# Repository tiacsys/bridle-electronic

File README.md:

# Bridle's Electronics Corner

<div style="display:flex;justify-content:right;">
<small><em>project update on: <strong>$Format:%cs$ with <mark><a href="https://github.com/tiacsys/bridle-electronic/commits/$Format:%h$" title="$Format:%B$" target="_blank">$Format:%h$</a></mark></strong></em></small>
</div>
<div style="display:flex;justify-content:right;">
<small><em>all data checked on <strong>2022-10-15</strong></em></small>
</div>

## About

This is a storage for all kinds of documentation like manuals, descriptions,
specifications, or datasheets around electronic devices and covers everything
from resistors, semiconductors, boards and assemblies up to finished devices.

## License

<span style="width:128px;float:right;">[![logo]][CC-BY-SA-4.0]</span>

[logo]: electronic/.logos/cc-by-sa.svg "CC-BY-SA"

See [``LICENSE.md``] and [``LICENSE-CC.md``] and also read carefully the
specific ``LICENSE`` or ``COPYRIGHT`` files found in all the subfolders,
if any exist there.

[CC-BY-SA-4.0]: https://creativecommons.org/licenses/by-sa/4.0 "Creative Commons Attribution-ShareAlike 4.0 International"
[``LICENSE-CC.md``]: electronic/LICENSE-CC.md "copy of CC-BY-SA-4.0"
[``LICENSE.md``]: electronic/LICENSE.md "project license"

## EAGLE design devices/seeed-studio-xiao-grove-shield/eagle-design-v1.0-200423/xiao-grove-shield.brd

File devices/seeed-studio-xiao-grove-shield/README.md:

# Grove Shield for Seeed Studio XIAO (Seeeduino XIAO)

<div style="display:flex;justify-content:right;">
<small><em>project update on: <strong>$Format:%cs$ with <mark><a href="https://github.com/tiacsys/bridle-electronic/commits/$Format:%h$" title="$Format:%B$" target="_blank">$Format:%h$</a></mark></strong></em></small>
</div>
<div style="display:flex;justify-content:right;">
<small><em>all data checked on <strong>2022-10-31</strong></em></small>
</div>

## About

<span style="width:256px;float:right;">[![board-iso]][board-iso]</span>

[board-iso]: electronic/devices/seeed-studio-xiao-grove-shield/board-iso.png "Grove Shield for Seeed Studio XIAO"

The **Grove Shield for Seeed Studio XIAO** is a plug-and-play Grove extension
board for [Seeed Studio XIAO][Seeed Studio XIAO SAMD21]. With the on-board power
regulator [ETA3410] and battery management chip [ETA6003] with the battery
bonding pad, you could easily power your Seeed Studio XIAO with lithium battery
and recharge it. 8 Grove connectors onboard includes two Grove I2C and one UART.
It acts as a bridge for Seeed Studio XIAO and [Seeed's Grove System][Grove System].
Flash SPI bonding pad allows you to add Flash to Seeed Studio XIAO to expand its
memory space, providing Seeed Studio XIAO with more possibilities.

[Grove System]: https://wiki.seeedstudio.com/Grove_System "What is the Grove System?"
[ETA3410]: http://www.eta-semi.com/product/1065.html "2A, 3MHz High Efficiency Step-Down Converter"
[ETA6003]: http://www.eta-semi.com/product/908.html "2.5A, 3MHz Switching Charger with Dynamic Power Path Management"

### Compact and Breakable Design

| Compact and Breakable Design |
|::|
| You could even break the board through the onboard PCB stamp holds according to your actual needs of the project (only 25mm x 39mm in dimension after break-off), making it smaller than smaller and the weight would be reduced from 13g to 10g as well! |
| <div style="background-color:white;">[![board-breakable-design]][board-breakable-design]</div> |

[board-breakable-design]: electronic/devices/seeed-studio-xiao-grove-shield/board-breakable-design.png "Grove Shield for Seeed Studio XIAO Breakable Design"

### Supported Boards

| Product | Pin Difference |
|:-|:-|
| [Seeed Studio XIAO SAMD21] | perfectly compatible |
| [Seeed Studio XIAO RP2040] | slightly different |
| [Seeed Studio XIAO ESP32C3] | slightly different |
| [Seeed Studio XIAO nRF52840] | slightly different |
| [Seeed Studio XIAO nRF52840] | slightly different |
| [Seeed Studio XIAO nRF52840 Sense][Seeed Studio XIAO nRF52840] | slightly different |

[Seeed Studio XIAO SAMD21]: index.php?dir=electronic/boards/seeed-studio-xiao-samd21 "Seeed Studio XIAO SAMD21 – Seeeduino XIAO"
[Seeed Studio XIAO RP2040]: index.php?dir=electronic/boards/seeed-studio-xiao-rp2040 "Seeed Studio XIAO RP2040"
[Seeed Studio XIAO ESP32C3]: index.php?dir=electronic/boards/seeed-studio-xiao-esp32c3 "Seeed Studio XIAO ESP32C3"
[Seeed Studio XIAO nRF52840]: index.php?dir=electronic/boards/seeed-studio-xiao-nrf52840 "Seeed Studio XIAO nRF52840"

## References

**EAN**: 6906142379964, 5903351247085<br/>
**UPC**:  906142379964<br/>
**SKU**: 103020312

**HSCODE**:   [8543.70.90.99]<br/>
**EUHSCODE**: [8543.70.90.99]<br/>
**USHSCODE**: [8471.49.00.00]<br/>
**COO**: CHINA

[8543.70.90.99]: https://www.tariffnumber.com/2022/85437090 "HS Code 85437090 – Electrical, machines, apparatus – Other"
[8471.49.00.00]: https://www.tariffnumber.com/2022/84714900 "HS Code 84714900 - Data, processing, machines – Other, presented in the form of systems"

*Brand*: Seeed<br/>
*Part number*: 103020312

* *HTML(2022-10-31)*: [Product Page] – *$4,50 (excl. VAT)*
* *HTML(2022-10-31)*: [Seeed Studio XIAO Series]
  – *Compact and powerful microcontroller*
* *HTML(2022-10-31)*: [Introduction of Grove]
  – *Grove makes it easier to connect, experiment, and simplify the prototyping process*
* *HTML(2022-10-31)*: [Overview of the Seeed Studio XIAO]
  – *Overview of the based Seeed Studio XIAO*

[Product Page]: https://www.seeedstudio.com/Grove-Shield-for-Seeeduino-XIAO-p-4621.html "Grove Shield for Seeed Studio XIAO"
[Seeed Studio XIAO Series]: https://www.seeedstudio.com/xiao-series-page "XIAO: thumb-sized tiny, but powerful"
[Introduction of Grove]: https://www.seeedstudio.com/getting-started.html "Grove: rapid prototyping"
[Overview of the Seeed Studio XIAO]: https://sigmdel.ca/michel/ha/xiao/seeeduino_xiao_01_en.html "Based Seeed Studio XIAO Overview"

| PCB Layer | PCB 3D or Footprint | PCB Populated (top & bottom) |
|::|::|::|
| <div style="background-color:white;"><div style="width:65%;display:inline-block">[![pcb-assembly-pcb]][pcb-assembly-pcb]</div></div> | <div style="background-color:black;"><div style="width:65%;display:inline-block">[![pcb-assembly-3d]][pcb-assembly-3d]</div></div> | <div style="background-color:white;">[![pcb-assembly-top]][pcb-assembly-top]</div> |
|  |  | <div style="background-color:white;">[![pcb-assembly-bot]][pcb-assembly-bot]</div> |

[pcb-assembly-pcb]: electronic/devices/seeed-studio-xiao-grove-shield/pcb-assembly-pcb.png "Grove Shield for Seeed Studio XIAO PCB Layer"
[pcb-assembly-3d]: electronic/devices/seeed-studio-xiao-grove-shield/pcb-assembly-3d.png "Grove Shield for Seeed Studio XIAO PCB 3D"
[pcb-assembly-top]: electronic/devices/seeed-studio-xiao-grove-shield/pcb-assembly-top.png "Grove Shield for Seeed Studio XIAO PCB Assembly (top)"
[pcb-assembly-bot]: electronic/devices/seeed-studio-xiao-grove-shield/pcb-assembly-bot.png "Grove Shield for Seeed Studio XIAO Assembly (bottom)"

## Documentation

* **PDF(2022-10-31)**: [Grove Shield for Seeed Studio XIAO with embedded battery management chip]
  – *[HTML(2022-10-31)](https://wiki.seeedstudio.com/Grove-Shield-for-Seeeduino-XIAO-embedded-battery-management-chip)*

[Grove Shield for Seeed Studio XIAO with embedded battery management chip]: electronic/devices/seeed-studio-xiao-grove-shield/getting-started.pdf "2022-10-31: Last updated on: August 19, 2021"

| Pinout |
|::|
| <div style="background-color:white;"><div style="width:75%;display:inline-block">[![board-pinout]][board-pinout]</div></div> |
| <div style="background-color:white;"><div style="width:75%;display:inline-block">[![board-interfaces]][board-interfaces]</div></div> |
| If you need, use the back of the Seeed Studio XIAO Grove Shield provisions pads for a SPI Flash memory in SOIC8 package. <br/> *Please soldering in right orientation, beginning with **PIN1** as shown below!* |
| <div style="background-color:white;"><div style="width:75%;display:inline-block">[![board-interface-flash]][board-interface-flash]</div></div> |

[board-pinout]: electronic/devices/seeed-studio-xiao-grove-shield/board-pinout.png "Grove Shield for Seeed Studio XIAO Pinout"
[board-interfaces]: electronic/devices/seeed-studio-xiao-grove-shield/board-interfaces.png "Grove Shield for Seeed Studio XIAO Interfaces"
[board-interface-flash]: electronic/devices/seeed-studio-xiao-grove-shield/board-interface-flash.png "Grove Shield for Seeed Studio XIAO Flash memory (SOIC8)"

* **PDF(2022-10-31)**: [Eagle Schematic v1.0 (200423)]
  – *[RAR(2022-10-31)](https://files.seeedstudio.com/wiki/Grove-Shield-for-Seeeduino-XIAO/res/Grove_Shield_for_Seeeduino_XIAO_v1.0.zip)*
  * **ZIP(2022-10-31)**: [Altium Design Data v1.0 (200423)][altium-design-v1.0-200423]
    – *[HTML(2022-10-31)](https://wiki.seeedstudio.com/Grove-Shield-for-Seeeduino-XIAO-embedded-battery-management-chip/#schematic-online-viewer)*

[Eagle Schematic v1.0 (200423)]: electronic/devices/seeed-studio-xiao-grove-shield/eagle-design-v1.0-200423/xiao-grove-shield-schematic.pdf "2022-10-31: Last updated on: April 23, 2020"

| Revision | Design Data | PCB Layout | Changelog |
|::|:-|::|:-|
| **v1.0** – *(September 2021)* | [eagle-design-v1.0-200423]:<br/>- [SCH-1-0]<br/>- [BRD-1-0] | <div style="background-color:black;"><div style="width:100%;display:inline-block">[![eagle-board-v1.0-200423]][eagle-board-v1.0-200423]</div></div> | Initail Version |
| | [altium-design-v1.0-200423]:<br/>- [PrjPcb-ZIP]<br/>- [STEP-1-0] | | |

[eagle-design-v1.0-200423]: index.php?dir=electronic/devices/seeed-studio-xiao-grove-shield/eagle-design-v1.0-200423 "Eagle Design Data"
[SCH-1-0]: electronic/devices/seeed-studio-xiao-grove-shield/eagle-design-v1.0-200423/xiao-grove-shield.sch "Eagle v9.3.1 Schematic"
[BRD-1-0]: electronic/devices/seeed-studio-xiao-grove-shield/eagle-design-v1.0-200423/xiao-grove-shield.brd "Eagle v9.3.1 Board"
[eagle-board-v1.0-200423]: electronic/devices/seeed-studio-xiao-grove-shield/eagle-design-v1.0-200423/xiao-grove-shield-pcb.svg "2022-10-31: Last updated on: April 23, 2020"

[altium-design-v1.0-200423]: index.php?dir=electronic/devices/seeed-studio-xiao-grove-shield/altium-design-v1.0-200423 "Altium Design Data"
[PrjPcb-ZIP]: electronic/devices/seeed-studio-xiao-grove-shield/altium-design-v1.0-200423/xiao-grove-shield-altium-designer.zip "Altium Designer Project Archive"
[STEP-1-0]: electronic/devices/seeed-studio-xiao-grove-shield/altium-design-v1.0-200423/xiao-grove-shield-pcb.step "Open CASCADE STEP processor 6.8"

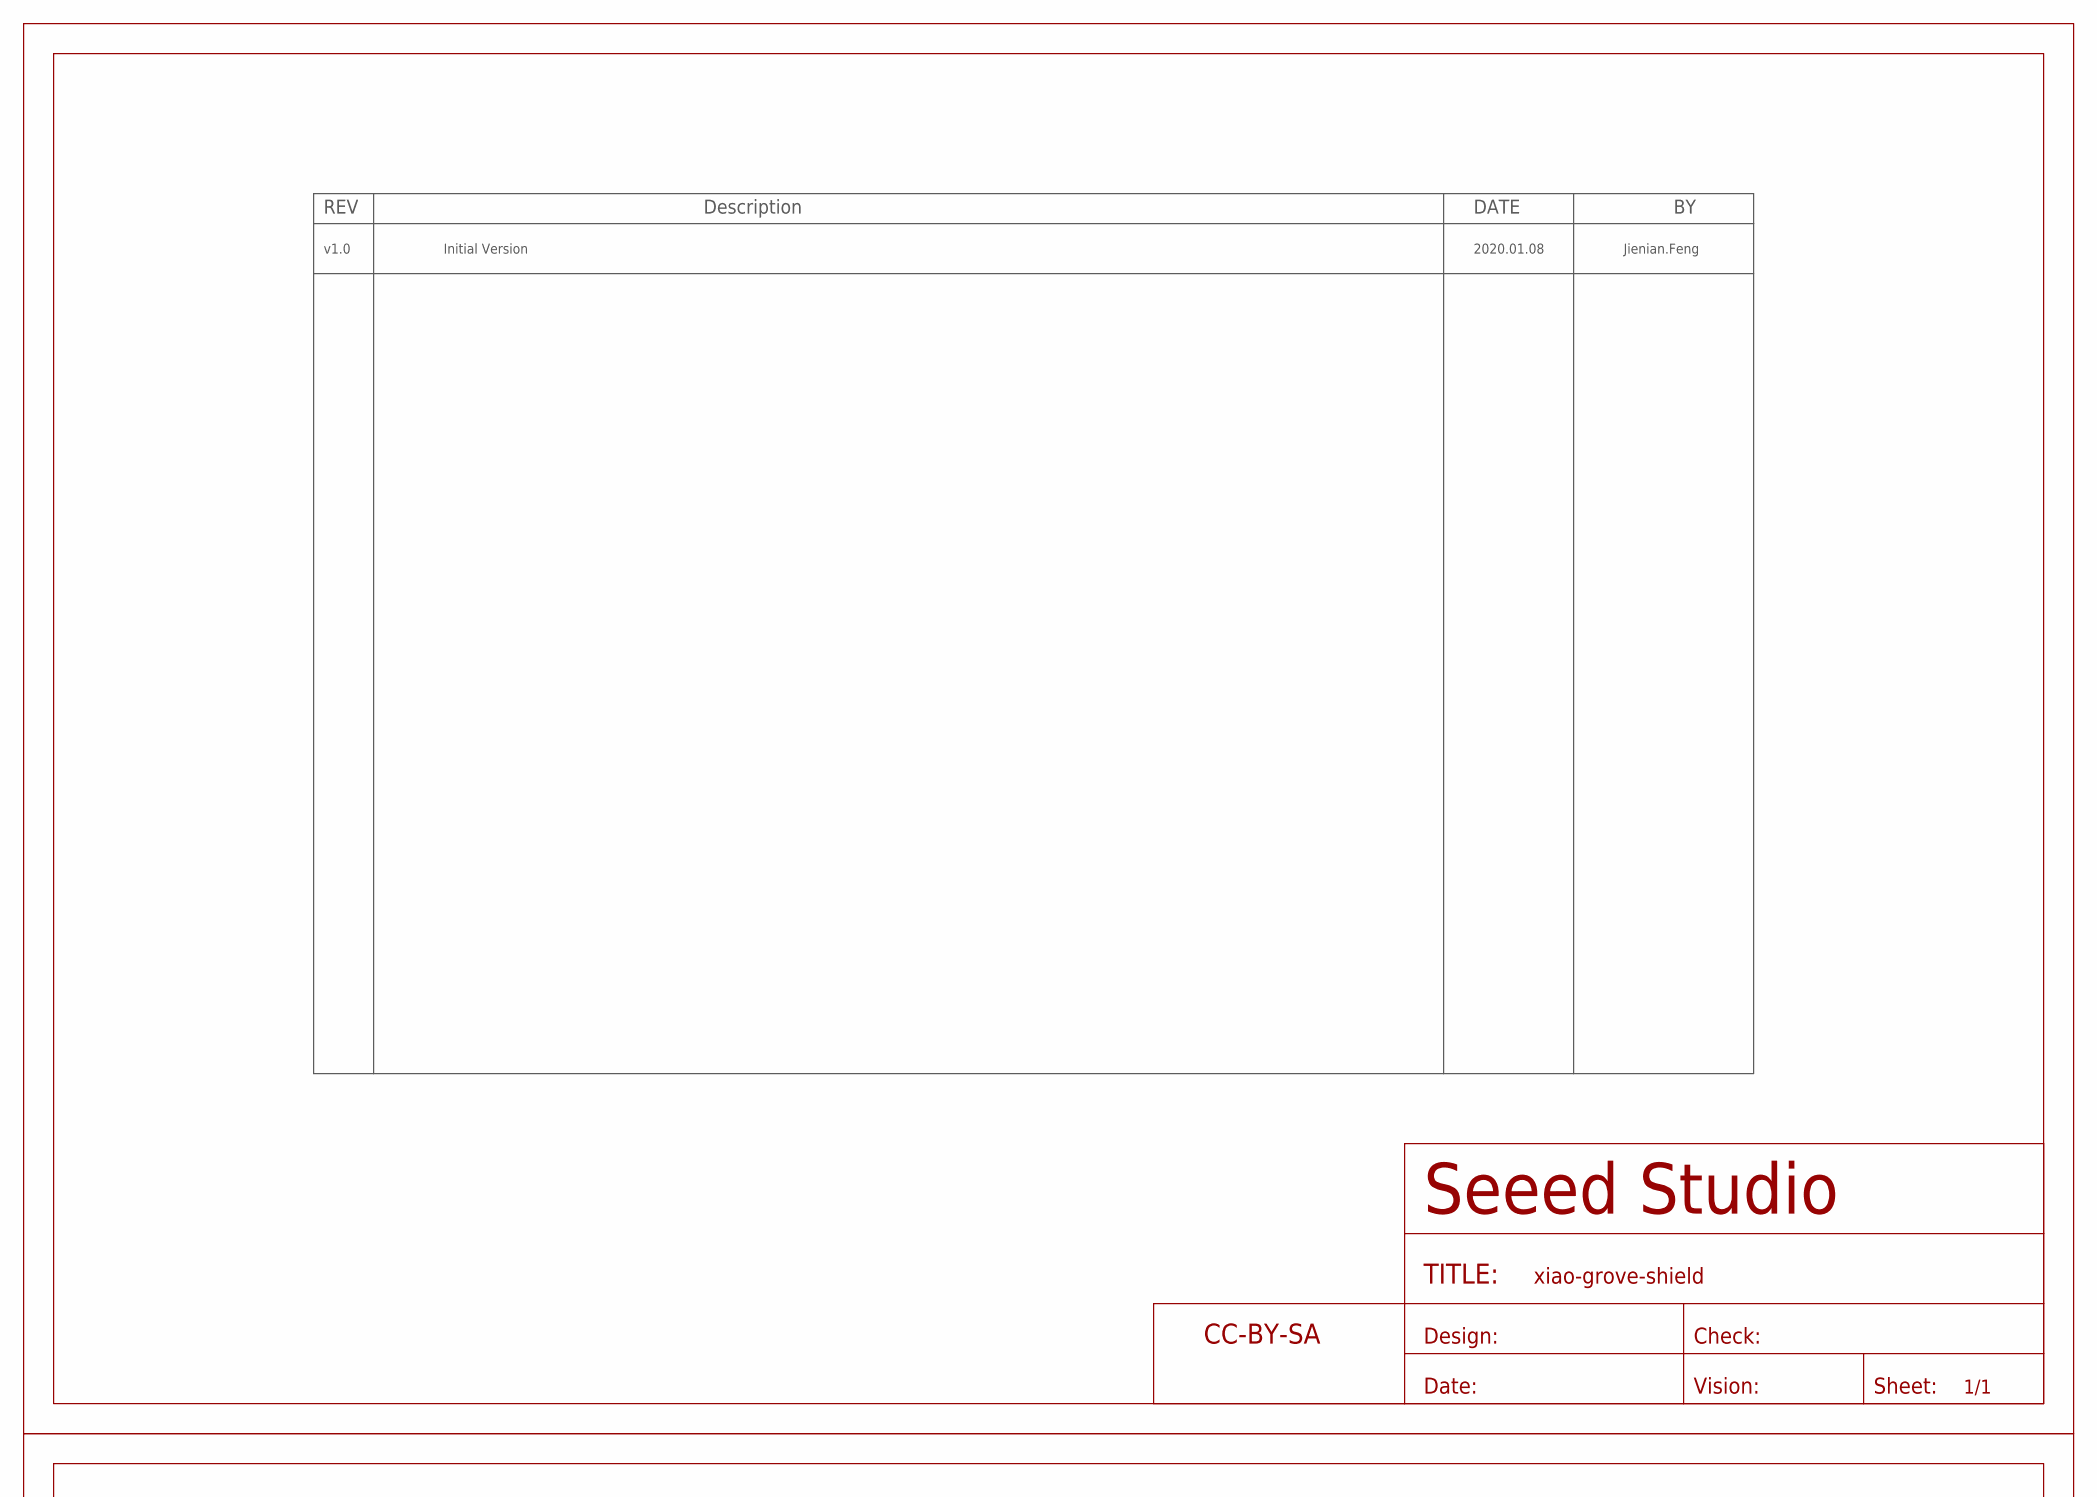
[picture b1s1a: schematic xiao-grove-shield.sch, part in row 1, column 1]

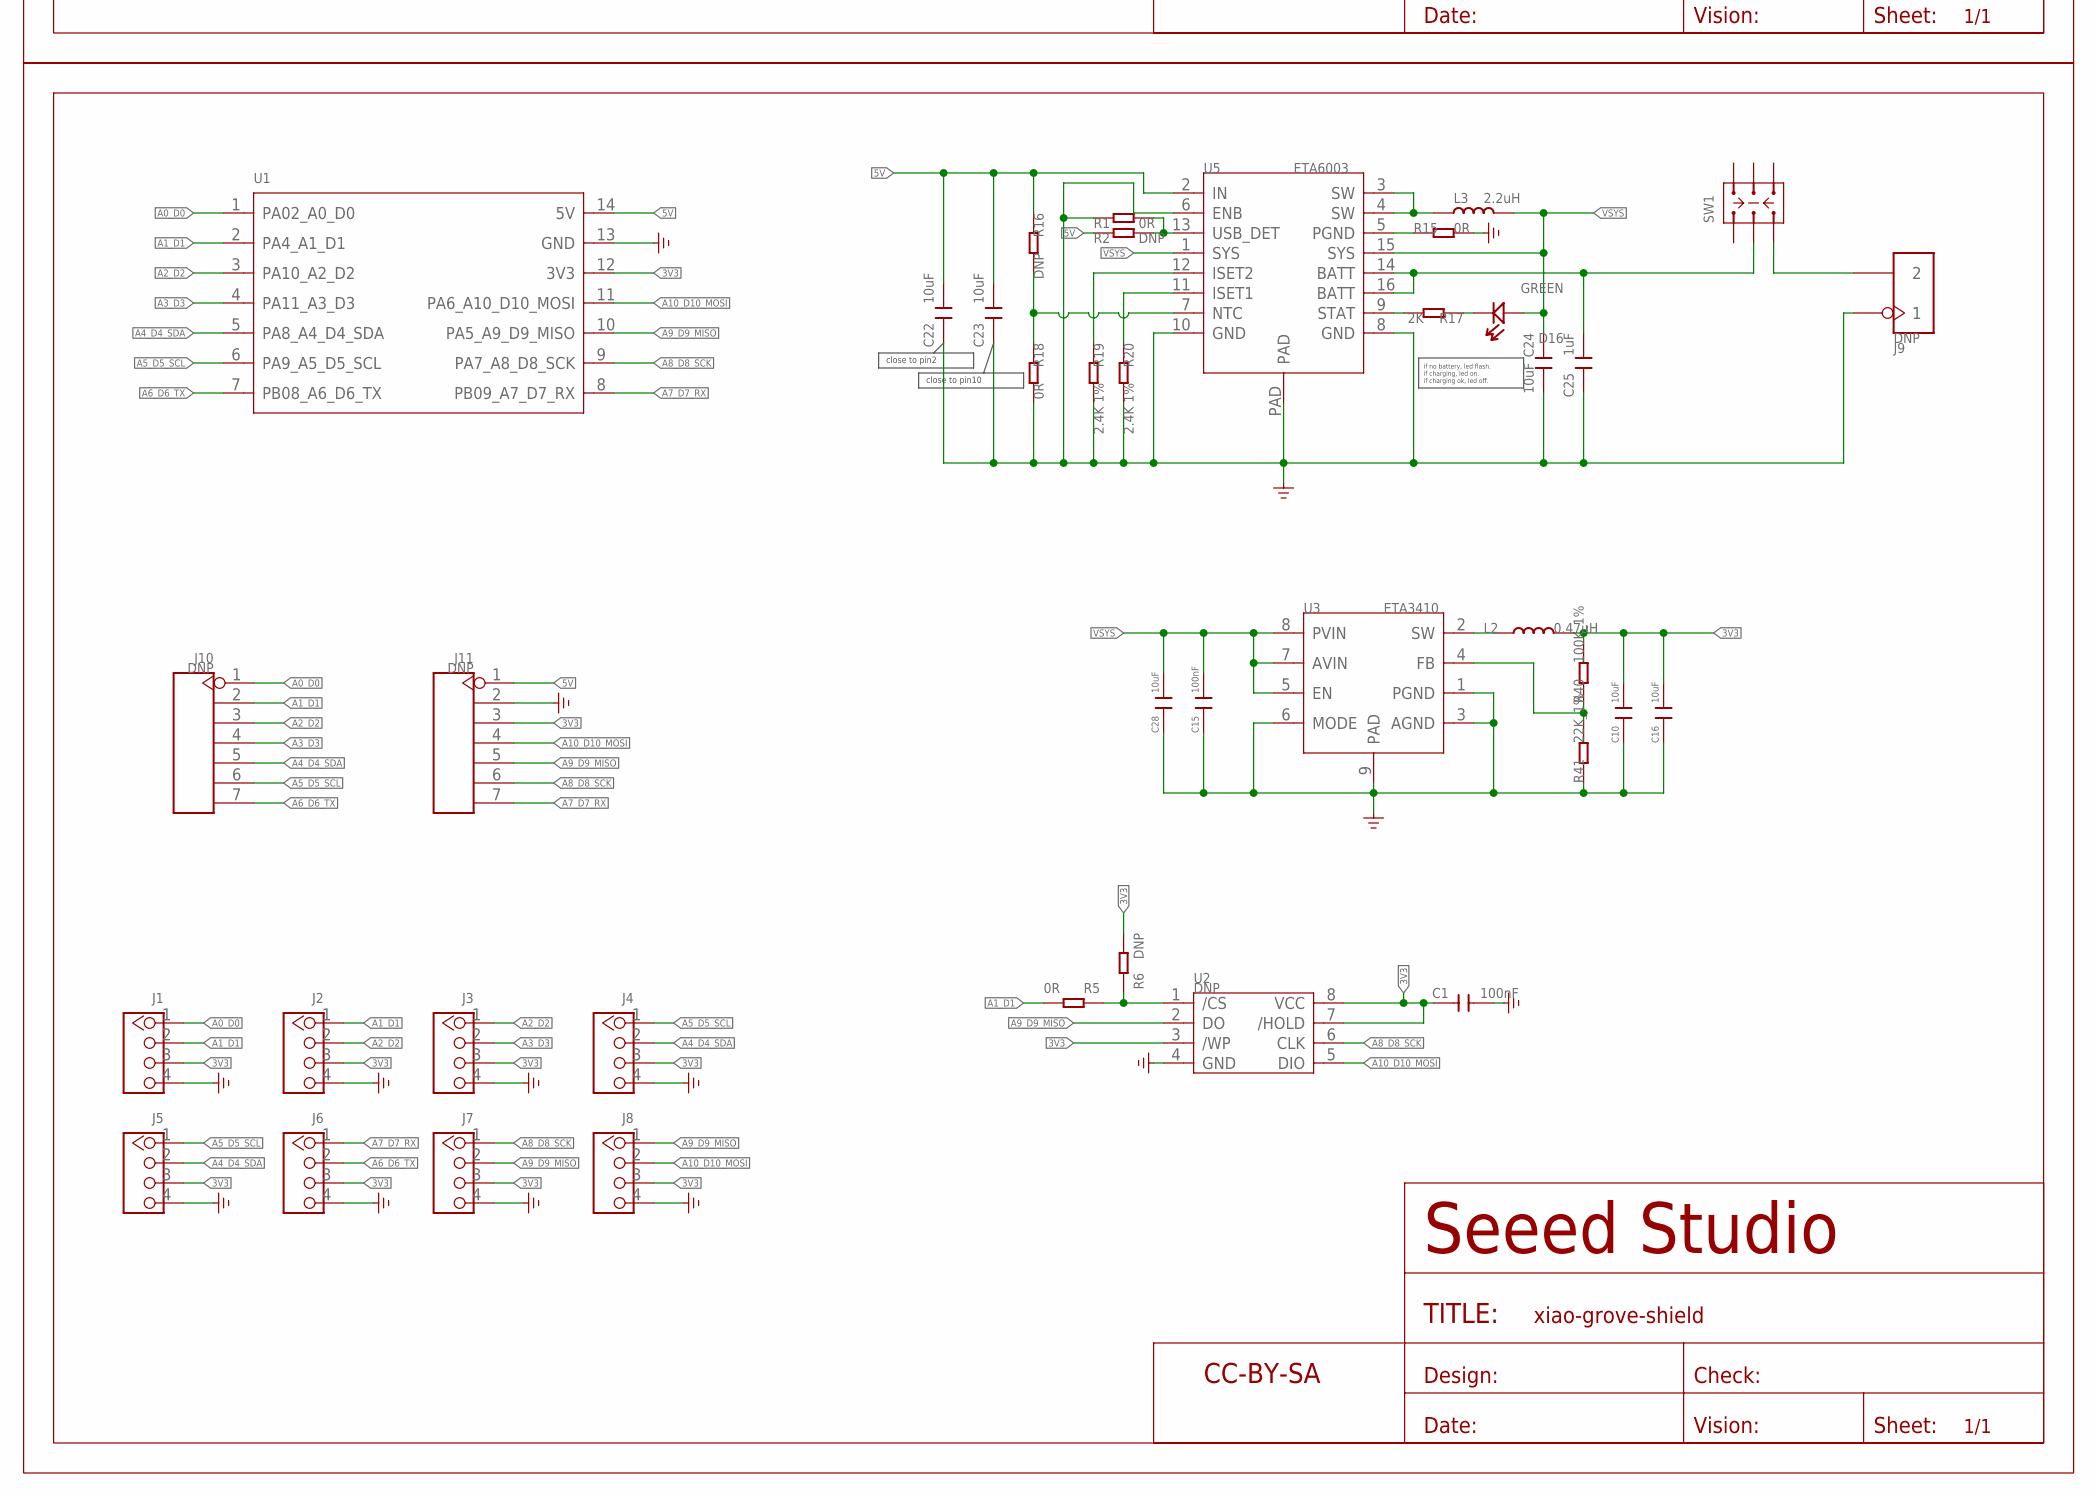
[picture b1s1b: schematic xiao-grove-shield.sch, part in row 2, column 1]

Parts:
C1, C15: 100nF; C0402
C10, C16, C22, C23, C24, C28: 10uF; C0603
C25: 1uF; C0402
D16: GREEN; LED-0402
FR1, FR2: SEEEDSTUDIO-OPEN-SCH-FRAME; SEEEDSTUDIO-PCB-FRAME
J1, J2, J3, J4, J5, J6, J7, J8: GROVE-CONNECTOR-DIP-320110033; HW4-2.0
J9: DNP; H2-2.0-C50D30MIL
J10, J11: DNP; H7-2.54
L2: 0.47uH; L201610
L3: 2.2uH; L0805
R1, R5, R15, R18: 0R; R0402
R2, R6, R16: DNP; R0402
R17: 2K; R0402
R19, R20: 2.4K 1%; R0402
R40: 100K_1%; R0402
R41: 22K_1%; R0402
SW1: SWITCH-2CH-6P-311030004; SW6-2.54-9.0X3.5X3.2MM-90D
U1: MOUDLE-SEEEDUINO-XIAO-DIP; MOUDLE14P-2.54-21X17.8MM
U2: DNP; SOIC8-1.27-5.3X5.3MM
U3: ETA3410; DFN8G-0.5-2X2MM
U5: ETA6003; QFN16GA-0.5-3X3MM

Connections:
3V3: C1.2, C10.2, C16.2, J1.3, J2.3, J3.3, J4.3, J5.3, J6.3, J7.3, J8.3, J11.3, L2.2, R6.1, R40.2, U1.12 (3V3), U2.3 (/WP), U2.7 (/HOLD), U2.8 (VCC)
5V: C22.1, C23.1, J11.1, R2.1, R16.1, U1.14 (5V), U5.2 (IN)
A0_D0: J1.1, J10.1, U1.1 (PA02_A0_D0)
A1_D1: J1.2, J2.1, J10.2, R5.1, U1.2 (PA4_A1_D1)
A2_D2: J2.2, J3.1, J10.3, U1.3 (PA10_A2_D2)
A3_D3: J3.2, J10.4, U1.4 (PA11_A3_D3)
A4_D4_SDA: J4.2, J5.2, J10.5, U1.5 (PA8_A4_D4_SDA)
A5_D5_SCL: J4.1, J5.1, J10.6, U1.6 (PA9_A5_D5_SCL)
A6_D6_TX: J6.2, J10.7, U1.7 (PB08_A6_D6_TX)
A7_D7_RX: J6.1, J11.7, U1.8 (PB09_A7_D7_RX)
A8_D8_SCK: J7.1, J11.6, U1.9 (PA7_A8_D8_SCK), U2.6 (CLK)
A9_D9_MISO: J7.2, J8.1, J11.5, U1.10 (PA5_A9_D9_MISO), U2.2 (DO)
A10_D10_MOSI: J8.2, J11.4, U1.11 (PA6_A10_D10_MOSI), U2.5 (DIO)
GND: C1.1, C10.1, C15.1, C16.1, C22.2, C23.2, C24.2, C25.2, C28.1, J1.4, J2.4, J3.4, J4.4, J5.4, J6.4, J7.4, J8.4, J9.1, J11.2, R1.1, R15.2, R18.2, R19.2, R20.2, R41.1, U1.13 (GND), U2.4 (GND), U3.1 (PGND), U3.3 (AGND), U3.6 (MODE), U3.9 (PAD), U5.6 (ENB), U5.8 (GND), U5.10 (GND), U5.PAD
unnamed: R1.2, R2.2, U5.13 (USB_DET)
unnamed: J9.2, SW1.CH1B
unnamed: R5.2, R6.2, U2.1 (/CS)
unnamed: C25.1, SW1.COM1, U5.14 (BATT), U5.16 (BATT)
unnamed: R40.1, R41.2, U3.4 (FB)
unnamed: L3.1, U5.3 (SW), U5.4 (SW)
unnamed: L2.1, U3.2 (SW)
unnamed: D16.-, R17.1
unnamed: R17.2, U5.9 (STAT)
unnamed: R16.2, R18.1, U5.7 (NTC)
unnamed: R20.1, U5.11 (ISET1)
unnamed: R19.1, U5.12 (ISET2)
unnamed: R15.1, U5.5 (PGND)
VSYS: C15.2, C24.1, C28.2, D16.+, L3.2, U3.5 (EN), U3.7 (AVIN), U3.8 (PVIN), U5.1 (SYS), U5.15 (SYS)

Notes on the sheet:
v1.0
Initial Version
2020.01.08
Jienian.Feng
close to pin10
if no battery, led flash. if charging, led on. if charging ok, led off.
close to pin2

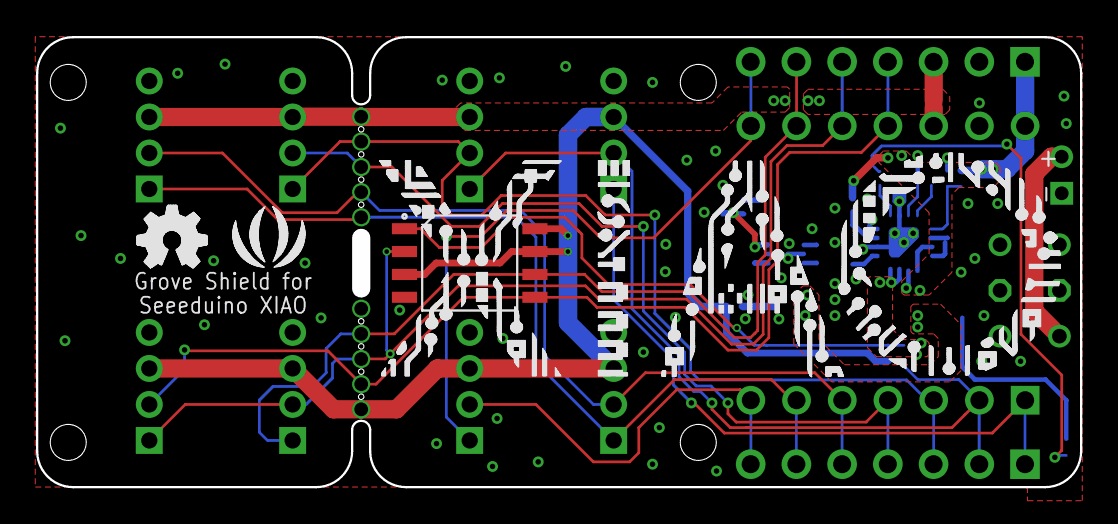
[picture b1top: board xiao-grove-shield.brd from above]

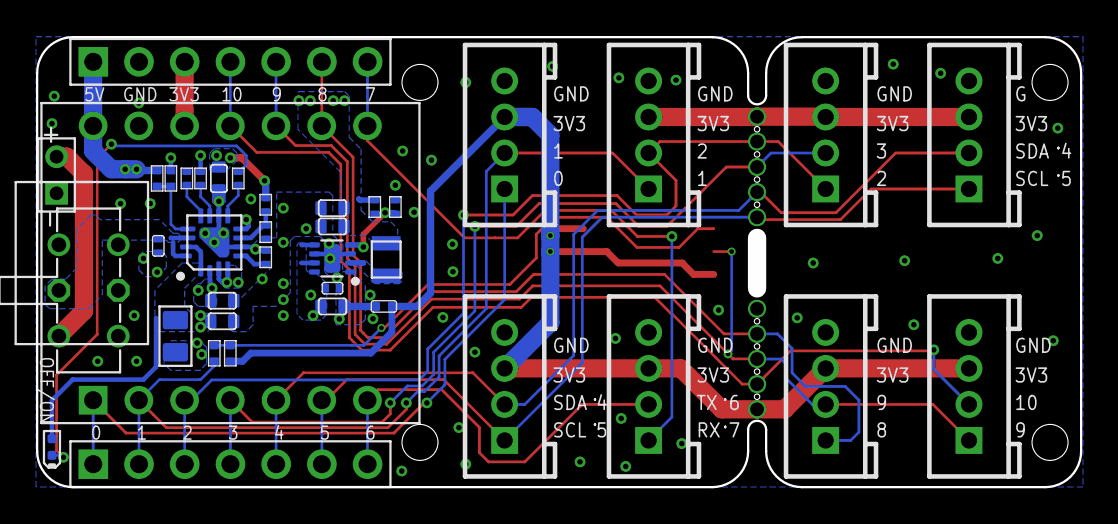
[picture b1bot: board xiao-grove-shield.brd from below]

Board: 2 copper layers, 58.0 x 25.0 mm, 42 parts (41 on the bottom side), 28 nets.

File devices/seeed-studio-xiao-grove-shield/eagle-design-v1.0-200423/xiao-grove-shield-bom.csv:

"Part";"Value";"Device";"Package";"Description";"";
"C1";"100nF";"CAP-0402";"C0402";"Ceramic Capacitors";"";
"C10";"10uF";"CAP-0603";"C0603";"Ceramic Capacitors";"";
"C15";"100nF";"C-0402";"C0402";"Ceramic Capacitors";"";
"C16";"10uF";"CAP-0603";"C0603";"Ceramic Capacitors";"";
"C22";"10uF";"CAP-0603";"C0603";"Ceramic Capacitors";"";
"C23";"10uF";"CAP-0603";"C0603";"Ceramic Capacitors";"";
"C24";"10uF";"CAP-0603";"C0603";"Ceramic Capacitors";"";
"C25";"1uF";"C-0402";"C0402";"Ceramic Capacitors";"";
"C28";"10uF";"CAP-0603";"C0603";"Ceramic Capacitors";"";
"D16";"GREEN";"LED-0402";"LED-0402";"";"";
"FR1";"SEEEDSTUDIO-OPEN-SCH-FRAME";"SEEEDSTUDIO-OPEN-SCH-FRAME";"SEEEDSTUDIO-PCB-FRAME";"";"";
"FR2";"SEEEDSTUDIO-OPEN-SCH-FRAME";"SEEEDSTUDIO-OPEN-SCH-FRAME";"SEEEDSTUDIO-PCB-FRAME";"";"";
"J1";"";"GROVE-CONNECTOR-DIP-320110033";"HW4-2.0";"";"";
"J2";"";"GROVE-CONNECTOR-DIP-320110033";"HW4-2.0";"";"";
"J3";"";"GROVE-CONNECTOR-DIP-320110033";"HW4-2.0";"";"";
"J4";"";"GROVE-CONNECTOR-DIP-320110033";"HW4-2.0";"";"";
"J5";"";"GROVE-CONNECTOR-DIP-320110033";"HW4-2.0";"";"";
"J6";"";"GROVE-CONNECTOR-DIP-320110033";"HW4-2.0";"";"";
"J7";"";"GROVE-CONNECTOR-DIP-320110033";"HW4-2.0";"";"";
"J8";"";"GROVE-CONNECTOR-DIP-320110033";"HW4-2.0";"";"";
"J9";"DNP";"HEADER-2P-50/30MIL";"H2-2.0-C50D30MIL";"";"";
"J10";"DNP";"HEADER-7P-2.54";"H7-2.54";"";"";
"J11";"DNP";"HEADER-7P-2.54";"H7-2.54";"";"";
"L2";"0.47uH";"L-MPM201610SR33_T";"L201610";"";"";
"L3";"2.2uH";"INDUCTOR/FERRITE-BEAD'0805'";"L0805";"";"";
"R1";"0R";"RES-0402";"R0402";"";"";
"R2";"DNP";"RES-0402";"R0402";"";"";
"R5";"0R";"RES-0402";"R0402";"";"";
"R6";"DNP";"RES-0402";"R0402";"";"";
"R15";"0R";"R-0402";"R0402";"";"";
"R16";"DNP";"R-0402";"R0402";"";"";
"R17";"2K";"R-0402";"R0402";"";"";
"R18";"0R";"R-0402";"R0402";"";"";
"R19";"2.4K 1%";"R-0402";"R0402";"";"";
"R20";"2.4K 1%";"R-0402";"R0402";"";"";
"R40";"100K_1%";"R-0402";"R0402";"";"";
"R41";"22K_1%";"R-0402";"R0402";"";"";
"SW1";"";"SWITCH-2CH-6P-311030004";"SW6-2.54-9.0X3.5X3.2MM-90D";"";"";
"U1";"";"MOUDLE-SEEEDUINO-XIAO-DIP";"MOUDLE14P-2.54-21X17.8MM";"";"";
"U2";"DNP";"FLASH-W25X80-SS";"SOIC8-1.27-5.3X5.3MM";"1M-BIT,2M-BIT,4M-BIT AND 8M-BIT SERIAL FLASH MEMORY WITH 4KB SECTORS AND DUAL OUTPUT SPI";"";
"U3";"ETA3410";"CONVERTER-ETA3410";"DFN8G-0.5-2X2MM";"3MHZ 2A High Step-Down Converter in DFN2x2-8L Package";"";
"U5";"ETA6003";"PMIC-ETA6003-310990023";"QFN16GA-0.5-3X3MM";"";"";

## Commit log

2022-10-14 initial startup with base project structure
    - directory structure with readmes
    - licensed under CC BY-SA 4.0
    - license comments
2022-10-14 ci: github: new workflow "Documentation Build"
2022-10-14 ci: github: new workflow "Documentation Remove"
2022-10-14 ci: github: new workflow "Documentation Publish"
    Will run once either "Documentation Build" or "Documentation Remove"
    completed with success; means there is a valid documentation monitor
    artifact that can be published.
2022-10-15 install Git LFS
2022-10-15 expand placeholders in all '*.md' files
2022-10-20 Injoinic Technology company
    - http://www.injoinic.com/company_info.html
    - http://www.injoinic.com/contact.html
2022-10-20 MakerHawk company
    - https://www.makerhawk.com/pages/about-us
    - https://www.makerhawk.com/pages/contact-us
2022-10-20 Injoinic Technology IP5306 component
    - http://www.injoinic.com/product_detail/id/21.html
2022-10-20 MakerHawk MH-CD42 (IP5306)
2022-10-20 Actinius Icarus SoM DK (nRF9160)
    - https://www.actinius.com/icarus-som-dk
2022-10-20 Actinius company with Getting Started
    - https://www.actinius.com/about
    - https://docs.actinius.com/getting-started
2022-10-20 refined project structure with companies
    Also add the new 'last update on: ...' footer on each MD file.
2022-10-20 Actinius Icarus SoM (nRF9160)
    - https://www.actinius.com/icarus-som
2022-10-20 Actinius Icarus IoT Board (nRF9160 Feather)
    - https://www.actinius.com/icarus
2022-10-20 Actinius Icarus Bee (nRF9160)
    - https://www.actinius.com/icarus-bee
2022-10-20 Circuit Dojo company
    - https://www.circuitdojo.org/
    - https://www.jaredwolff.com/about
    - https://www.jaredwolff.com/contact
2022-10-20 Circuit Dojo nRF9160 Feather
    - https://www.jaredwolff.com/store/nrf9160-feather
    - https://github.com/circuitdojo/nrf9160-feather
    - https://docs.jaredwolff.com/
    - https://github.com/circuitdojo/docs
2022-10-22 Extend git placeholder with link to GitHub history
2022-10-22 Seeed Studio company
    - https://www.seeedstudio.com/about_seeed
    - https://www.seeedstudio.com/contacts
2022-10-22 Seeed Studio XIAO SAMD21 - Seeeduino XIAO
    - https://www.seeedstudio.com/Seeeduino-XIAO-Arduino-Microcontroller-SAMD21-Cortex-M0+-p-4426.html
    - https://wiki.seeedstudio.com/Seeeduino-XIAO
2022-10-23 Seeed Studio XIAO RP2040
    - https://www.seeedstudio.com/XIAO-RP2040-v1-0-p-5026.html
    - https://wiki.seeedstudio.com/XIAO-RP2040
2022-10-23 Seeed Studio XIAO nRF52840 (Sense)
    - https://www.seeedstudio.com/Seeed-XIAO-BLE-nRF52840-p-5201.html
    - https://www.seeedstudio.com/Seeed-XIAO-BLE-Sense-nRF52840-p-5253.html
    - https://wiki.seeedstudio.com/XIAO-BLE-Sense-Getting-Started
    - https://wiki.seeedstudio.com/XIAO_BLE
2022-10-23 Seeed Studio XIAO ESP32C3
    - https://www.seeedstudio.com/Seeed-XIAO-ESP32C3-p-5431.html
    - https://wiki.seeedstudio.com/XIAO_ESP32C3_Getting_Started
2022-10-23 MEMSensing Microsystems company
    - https://www.memsensing.com/About_us.html
    - https://www.memsensing.com/contact.html
2022-10-23 MEMSensing MSM261D3526H1CPM component
    - http://en.memsensing.com/product/176.html
    - https://szwsdkj.com/article/minxinwei/42.html
    - https://www.denovocn.com/sites/default/files/MSM261D3526H1CPM.pdf
    - https://files.seeedstudio.com/wiki/XIAO-BLE/mic-MSM261D3526H1CPM-ENG.pdf
2022-10-23 Fix many typos and formattings in companies
2022-10-23 Makerdiary company
    - https://makerdiary.com/pages/about-us
    - https://makerdiary.com/pages/faqs
2022-10-23 Makerdiary nRF52840 MDK USB Dongle (PCBA)
    - https://makerdiary.com/collections/frontpage/products/nrf52840-mdk-usb-dongle-w-case
    - https://makerdiary.com/collections/frontpage/products/nrf52840-mdk-usb-dongle
    - https://wiki.makerdiary.com/nrf52840-mdk-usb-dongle
2022-10-23 Fix EAN and UPC numbers in boards and devices
2022-10-23 Add HTS code links for US, EU, and world
2022-10-23 Fiy typo in Makerdiary company
2022-10-26 Add more UI icons for DIR, DOC, CAB, WEB and Git
    DIR: - https://www.flaticon.com/free-icon/folder_5251763
    - https://www.flaticon.com/free-icon/folder_5251663
    DOC: - https://www.flaticon.com/free-icon/file_5251057
    - https://www.flaticon.com/free-icon/file_5251070
    CAB: - https://www.flaticon.com/free-icon/filling-cabinet_5254457
    - https://www.flaticon.com/free-icon/filling-cabinet_5253892
2022-10-26 Canaan Creative company
    - https://canaan.io/about
    - https://canaan-creative.com/about
    - https://canaan.io/products/avalonminer
    - https://canaan-creative.com/product/kendryteai
2022-10-26 SiPEED company
    - https://sipeed.com/
2022-10-26 SiPEED Maix-I M1/M1w – AI Core Module
    ... with Kendryte K210 and optional ESP8285
    - https://sipeed.com/solution-en.html
    - https://dl.sipeed.com/shareURL/MAIX
    - https://wiki.sipeed.com/hardware/zh/maix/core_module.html
2022-10-26 Canaan Kendryte K210 component
    - https://canaan.io/product/kendryteai
    - https://canaan.io/developer
    - https://github.com/kendryte
2022-10-27 Sitronix company
    - https://www.sitronix.com.tw/en/about/overview
    - https://www.sitronix.com.tw/en/contact-us
2022-10-27 Sitronix ST7789V component
    - https://www.sitronix.com.tw/en/products/aiot-device-ddi
2022-10-27 ILITEK company
    - http://www.ilitek.com/page/about/index.aspx?kind=1
    - http://www.ilitek.com/page/about/index.aspx?kind=43
2022-10-27 ILITEK ILI9341(V) component
    - http://www.ilitek.com/page/about/index.aspx?kind=9
2022-10-27 use Git LFS for RAR and ARJ archives
2022-10-27 LCD TFT 2.4" 240x320 RGB262K 24P 0.5 FPC 8bit MCU
    - RY24049B-00-A
    - JLT24100B-V1
    - ZSX024-B2441-V1
2022-10-29 use Git LFS for DWG and DXB files
2022-10-29 OmniVision company
    - https://www.ovt.com/company/about-us
    - https://www.ovt.com/company/contact-us
2022-10-29 GalaxyCore company
    - https://www.gcoreinc.com/about
    - https://www.gcoreinc.com/about/contact
2022-10-29 CAM CIS VGA 640x480 10bit ADC 8bit DVP
    - ZV-T01-GA4.2
    - ZV-T01-GA4.4
    - ZV-Sipeed-GA4A4.3
    - ZV-Sipeed-GA4A4.4
2022-10-29 GC0328 component
    - https://www.gcoreinc.com/products/index?cid=2&subcid=6
2022-10-29 OV2640 component
    - http://web.archive.org/web/20111014200352/http://ovt.com/products/sensor.php?id=3
2022-10-29 Widora (Waidora in spoken language) company
    ... the people behind 'Mango Pi'.
    - https://widora.io/
    - https://widora.cn/
    - https://mangopi.org/
2022-10-29 CAM CIS UXGA 1600x1200 10bit ADC 8/10bit DVP
    - RYS-2640-M7
    - HDF3M-811XR
    - DCX-OV2640-V2
    - OV2640-75MM
    - Waveshare-JT-HJ-376
2022-10-29 SiPEED Maix-I: remove translator's watermark
2022-10-29 Titan Micro Electronics (Tianwei) company
    - http://www.titanmec.com/index.php/about/index/typeid/34.html
    - http://www.titanmec.com/index.php/about/index/typeid/5.html
2022-10-29 TM8211 component
    - http://www.titanmec.com/index.php/product/view/id/609.html
2022-10-29 MSM261S4030H0 component
    - http://en.memsensing.com/product/176.html
2022-10-29 Nsiway (Naxinwei in spoken language) company
    - http://www.nsiway.com.cn/intro/4.html
    - http://www.nsiway.com.cn/contact.html
2022-10-29 NS4150 component
    - http://www.nsiway.com.cn/product/5/
    - http://www.nsiway.com.cn/product/44.html
    - http://www.nsiway.com.cn/product/58.html
2022-10-29 SiPEED MaixDuino (Kit) for RISC-V AI + IoT
    - https://sipeed.com/solution-en.html
    - https://dl.sipeed.com/shareURL/MAIX/HDK/Sipeed-Maixduino
    - https://dl.sipeed.com/shareURL/MAIX/Maixduino
    - https://wiki.sipeed.com/hardware/zh/maix/maixpy_develop_kit_board/maix_duino.html
    - https://wiki.sipeed.com/soft/maixpy/zh/develop_kit_board/maix_duino.html
2022-11-01 Seeed Studio XIAO Grove Shield
    - https://www.seeedstudio.com/Grove-Shield-for-Seeeduino-XIAO-p-4621.html
    - https://wiki.seeedstudio.com/Grove-Shield-for-Seeeduino-XIAO-embedded-battery-management-chip
2022-11-01 Seeed Studio XIAO Expansion Board
    - https://www.seeedstudio.com/Seeeduino-XIAO-Expansion-board-p-4746.html
    - https://wiki.seeedstudio.com/Seeeduino-XIAO-Expansion-Board
2023-06-22 add new category for full and complete systems
2023-06-22 Gigatron TTL
    - https://gigatron.io/
2023-07-17 MyCPU v2.3
    - http://www.mycpu.eu/
2023-07-17 Agon light™ and AgonLight2
    - https://www.thebyteattic.com/p/agon.html
2023-07-18 ci: github: use dawidd6/action-download-artifact@v2
2023-07-19 ci: github: use Node.js piped stream for artifact

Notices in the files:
parts and their libraries:
moudle-new: This work is licensed under the Creative Commons Attribution 4.0 International License.
To view a copy of this license,visit:
http://creativecommons.org/licenses/by-sa/4.0
